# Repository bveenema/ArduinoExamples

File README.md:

# Mix Controller
A chrome extension user interface and embedded firmware for controlling mixing pumps.

#### Index
1. User Interface (Chrome Extension)
  * [Installation](#installation)
  * [Create Shortcuts](#create-shortcuts)
  * [How to Use](#how-to-use)
1. Firmware (Mixer Software)
  * [Driver Installation](#driver-installation)

## User Interface (Chrome Extension)
### Installation
To install the user interface:
1. Download the CRX file from the latest release
  - Go to [MixController/releases](https://github.com/bveenema/MixController/releases)
  - Click the **.crx** file in this *Assets* of the latest realese
  ![Img of where to download CRX file][JPG_downloadCRX]

2. Open the **Extensions** page in Chrome
![Type "chrome://extensions" in the address bar][JPG_GoToExtensions]

3. Install the App
  - Click and drag the CRX file into the *Extensions* window
  ![Install the App][JPG_installApp]

4. Accept the Permsions
  - Mix Controller requires access to your computers serial devices, click *Add App* to approve
  ![Img of Accept Permissions][JPG_acceptPermissions]

5. See [App Readme](https://github.com/bveenema/MixController/blob/master/Chrome%20Extension/README.md) for information on launching and using the app

### Create Shortcuts
To create Desktop/Start Menu/Taskbar shortcuts:
1. Click **Details** under Mix Controller, select **Create Shortcuts...** , select or deselect the shortcuts you want to create , click **Create**
![How to create shortcuts][JPG_CreateShortcuts]

## Firmware (Mixer Software)
### Driver Installation
In order to communicate with the Mixer Software, the drivers must be installed on first. Installing drivers is done by installing Particle CLI, a package of software that includes Particle drivers (which the Mixer Software runs on)

###### For Mac or Linux
---

Open Terminal, or preferred terminal program and paste this command to install the Particle CLI:

``` terminal
bash <( curl -sL https://particle.io/install-cli )
```

You may need to open a new terminal after the install completes to use the particle command.

If you get a message about installing dfu-util for your OS, make sure you have [homebrew](https://brew.sh/) installed and run the command above again.

###### For Windows
---
Download the [Windows CLI Installer](https://binaries.particle.io/cli/installer/windows/ParticleCLISetup.exe) and run it to install the Particle CLI, the device drivers and the dependencies that the CLI needs.

*Optional*: On the **Choose Components** screen, un-Select "CLI" and "OpenSSL (keys tools)" to install only the USB drivers.

[JPG_downloadZIP]: ReadmeAssets/DownloadZip.jpg "How to download ZIP"
[JPG_GoToExtensions]: ReadmeAssets/GoToExtensions.jpg "Or type \"chrome://extensions\" in the address bar"
[JPG_LoadUnpackedExtension]: ReadmeAssets/LoadUnpackedExtension.jpg "Check the box next to \"Developer Mode\" and then click \"Load unpacked extension\""
[JPG_MixControllerExtension]: ReadmeAssets/MixControllerExtension.jpg "Mix Controller Extension"
[JPG_CreateShortcuts]: ReadmeAssets/CreateShortcuts.jpg "How to create shortcuts"
[JPG_downloadCRX]: ReadmeAssets/downloadCRX.jpg "Where to download CRX"
[JPG_installApp]: ReadmeAssets/installApp.jpg "Click and drag to install"
[JPG_acceptPermissions]: ReadmeAssets/acceptPermission.jpg "Click Add App to accept serial permissions"

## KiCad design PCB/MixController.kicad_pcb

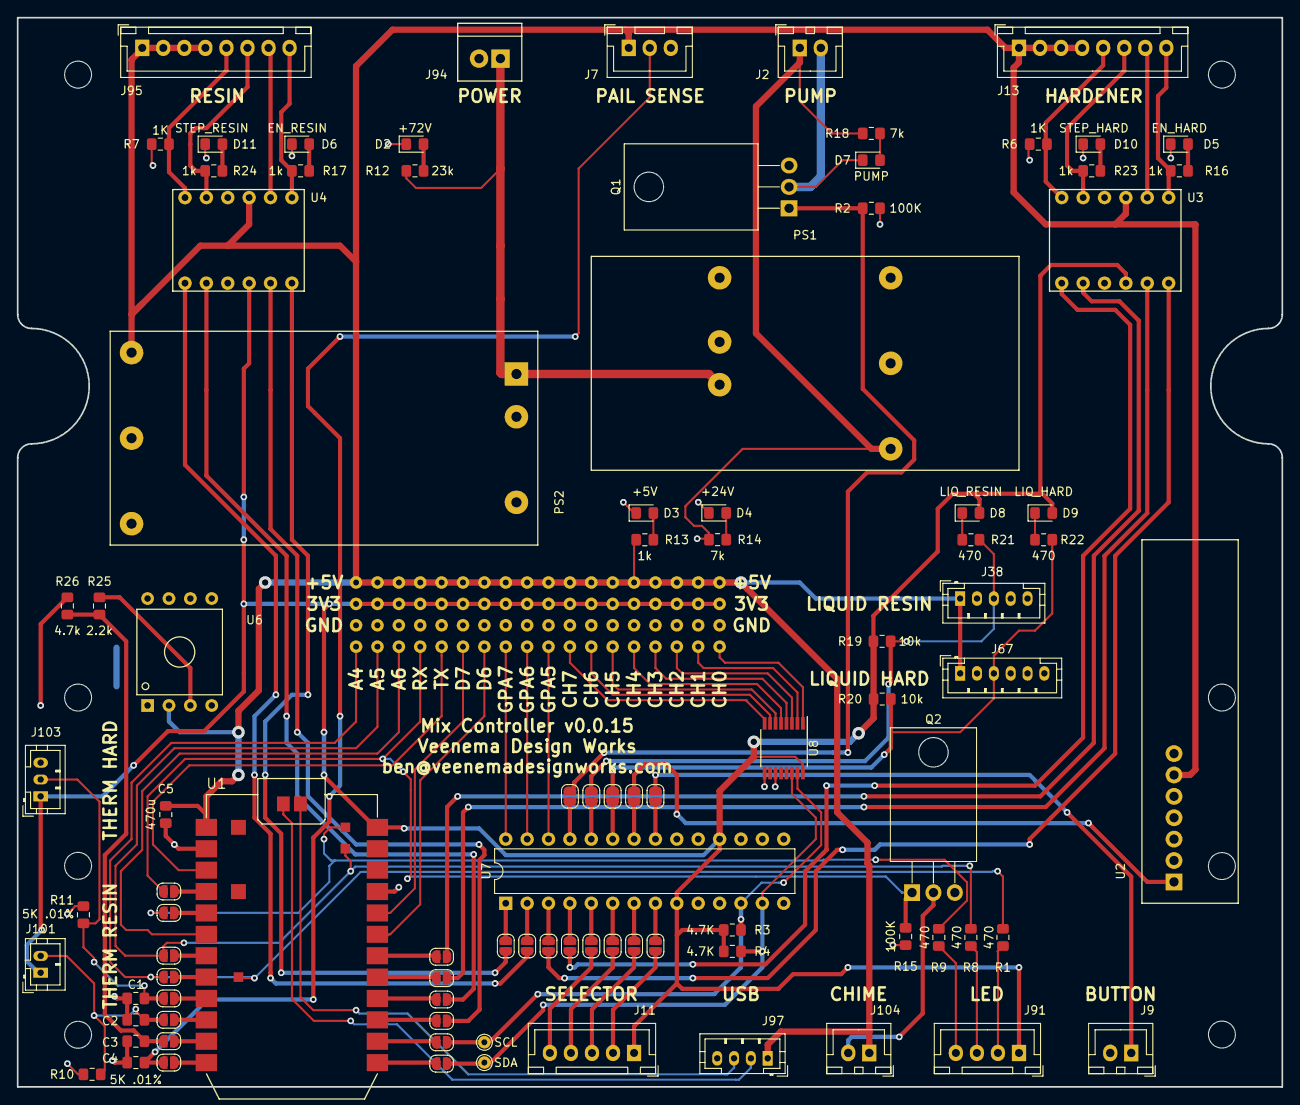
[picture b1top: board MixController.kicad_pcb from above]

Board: 2 copper layers, 150.2 x 127.0 mm, 166 parts (0 on the bottom side), 100 nets.

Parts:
C1, C2, C3, C4: 0.1u; C_0805_2012Metric_Pad1.15x1.40mm_HandSolder
C5: 470u; C_0805_2012Metric_Pad1.15x1.40mm_HandSolder
D2: +72V; LED_0805_2012Metric_Pad1.15x1.40mm_HandSolder
D3: +5V; LED_0805_2012Metric_Pad1.15x1.40mm_HandSolder
D4: +24V; LED_0805_2012Metric_Pad1.15x1.40mm_HandSolder
D5: EN_HARD; LED_0805_2012Metric_Pad1.15x1.40mm_HandSolder
D6: EN_RESIN; LED_0805_2012Metric_Pad1.15x1.40mm_HandSolder
D7: PUMP; LED_0805_2012Metric_Pad1.15x1.40mm_HandSolder
D8: LIQ_RESIN; LED_0805_2012Metric_Pad1.15x1.40mm_HandSolder
D9: LIQ_HARD; LED_0805_2012Metric_Pad1.15x1.40mm_HandSolder
D10: STEP_HARD; LED_0805_2012Metric_Pad1.15x1.40mm_HandSolder
D11: STEP_RESIN; LED_0805_2012Metric_Pad1.15x1.40mm_HandSolder
J2, J9, J104: B2B-XH-A(LF)(SN); JST_XH_B02B-XH-A_1x02_P2.50mm_Vertical
J7: B3B-XH-A(LF)(SN); JST_XH_B03B-XH-A_1x03_P2.50mm_Vertical
J11: B5B-XH-A(LF)(SN); JST_XH_B05B-XH-A_1x05_P2.50mm_Vertical
J13, J95: B8B-XH-A(LF)(SN); JST_XH_B08B-XH-A_1x08_P2.50mm_Vertical
J15, J16, J17, J18, J19, J20, J21, J22, J23, J24, J25, J26, J27, J28, J29, J30, J31, J32, J33, J34, J35, J36, J37, J39, J40, J41, J42, J43, J44, J45, J46, J47, J48, J49, J50, J51, J52, J53, J54, J56, J57, J58, J59, J60, J61, J62, J63, J64, J65, J66, J68, J69, J70, J72, J73, J74, J75, J76, J77, J78, J79, J80, J81, J82, J83, J84, J85, J86, J87, J88, J89, J90: ConnectorPoint_THT_D1.5mm_Drill-0.7mm
J38: B5B-PH-K-S(LF)(SN); JST_PH_B5B-PH-K_1x05_P2.00mm_Vertical
J67: B6B-PH-K-S(LF)(SN); JST_PH_B6B-PH-K_1x06_P2.00mm_Vertical
J91: B4B-XH-A(LF)(SN); JST_XH_B04B-XH-A_1x04_P2.50mm_Vertical
J94: 0705430001; Molex-705430001_02x2.54mm_Straight
J97: B4B-PH-K-S(LF)(SN); JST_PH_B4B-PH-K_1x04_P2.00mm_Vertical
J101: B2B-PH-K-S(LF)(SN); JST_PH_B2B-PH-K_1x02_P2.00mm_Vertical
J103: B3B-PH-K-S(LF)(SN); JST_PH_B3B-PH-K_1x03_P2.00mm_Vertical
JP1, JP2, JP3, JP4, JP5, JP6, JP7, JP8, JP9, JP10, JP11, JP12, JP13, JP14, JP15, JP16, JP17, JP18, JP19, JP20, JP21, JP22, JP23, JP24, JP25, JP26, JP27: SolderJumper-2_P1.3mm_Open_RoundedPad1.0x1.5mm
PS1: ERM01H110
PS2: RSDW20H-05; RSDW20_H
Q1, Q2: Q_NMOS_GDS; TO-220-3_Horizontal_TabDown
R1, R8, R9, R21, R22: 470; R_0805_2012Metric_Pad1.15x1.40mm_HandSolder
R2, R15: 100K; R_0805_2012Metric_Pad1.15x1.40mm_HandSolder
R3, R4: 4.7K; R_0805_2012Metric_Pad1.15x1.40mm_HandSolder
R6, R7: 1K; R_0805_2012Metric_Pad1.15x1.40mm_HandSolder
R10, R11: 5K .01%; R_0805_2012Metric_Pad1.15x1.40mm_HandSolder
R12: 23k; R_0805_2012Metric_Pad1.15x1.40mm_HandSolder
R13, R16, R17, R23, R24: 1k; R_0805_2012Metric_Pad1.15x1.40mm_HandSolder
R14, R18: 7k; R_0805_2012Metric_Pad1.15x1.40mm_HandSolder
R19, R20: 10k; R_0805_2012Metric_Pad1.15x1.40mm_HandSolder
R25: 2.2k; R_0805_2012Metric_Pad1.15x1.40mm_HandSolder
R26: 4.7k; R_0805_2012Metric_Pad1.15x1.40mm_HandSolder
TP1: SCL; TestPoint_THTPad_D1.5mm_Drill0.7mm
TP2: SDA; TestPoint_THTPad_D1.5mm_Drill0.7mm
U1: Photon; photon_smd
U2: Adafruit_1096; SimpleRF_Receiver
U3, U4: BOB-12009; BOB-12_W10.16mm
U6: HSCDANN005PGAA5; HoneyWell_DIP_AN
U7: MCP23017_SP; DIP-28_W7.62mm
U8: ADS7830; TSSOP-16_4.4x5mm_P0.65mm

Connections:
+3V3: D8.2, D9.2, J11.1, J20.1, J21.1, J22.1, J23.1, J24.1, J47.1, J48.1, J49.1, J50.1, J51.1, J52.1, J53.1, J54.1, J56.1, J57.1, J58.1, J87.1, J88.1, J91.1, J101.1, J103.1, R3.1, R4.1, R19.1, R20.1, U1.24, U3.4, U4.4, U7.9, U7.18, U8.16
+5V: C5.2, J7.1, J13.1, J13.2, J13.3, J13.4, J15.1, J16.1, J17.1, J18.1, J19.1, J30.1, J31.1, J32.1, J33.1, J34.1, J35.1, J36.1, J37.1, J38.1, J39.1, J40.1, J41.1, J67.1, J89.1, J90.1, J95.1, J95.2, J95.3, J95.4, J97.1, J104.1, PS2.3, R13.1, U1.1, U2.6, U3.9, U4.9, U6.2
+24V: J2.1, PS1.4, R14.2, R18.2
+72V: J94.1, PS1.1, PS2.1, R12.2
/CHIME: J43.1, JP26.1, Q2.1, R15.1
/HARDENER_ENABLE: JP8.1, U3.6
/HARDENER_HLFB: JP9.1, U3.1
/HARDENER_INPUT_DIR: JP19.2, U3.5
/HARDENER_INPUT_STEP: JP18.2, U3.2
/LIQUID_SNS_HARDENER: J67.3, JP16.1, R20.2, R22.1
/LIQUID_SNS_RESIN: J38.3, JP17.1, R19.2, R21.1
/PAIL_SNS: C4.2, J7.2, JP5.1
/PRESS_SNS: C3.2, JP4.1, R25.2, R26.1
/PUMP_EN: JP27.1, Q1.1, R2.1
/RESIN_ENABLE: JP6.1, U4.6
/RESIN_HLFB: JP7.1, U4.1
/RESIN_INPUT_DIR: JP21.2, U4.5
/RESIN_INPUT_STEP: JP20.2, U4.2
/ROTARY_1: J11.2, JP13.1
/ROTARY_2: J11.3, JP12.1
/ROTARY_3: J11.4, JP11.1
/ROTARY_4: J11.5, JP10.1
/SCL: JP22.2, R3.2, TP1.1, U7.12, U8.15
/SDA: JP23.2, R4.2, TP2.1, U7.13, U8.14
/STATUS_LED_B: JP1.1, R9.1, U1.29
/STATUS_LED_G: J45.1, JP2.1, R8.1, U1.28
/STATUS_LED_R: J46.1, JP3.1, R1.1, U1.27
/THERM_HARDENER: C1.2, J103.2, JP24.1, R11.1
/THERM_RESIN: C2.2, J101.2, JP25.1, R10.1
/USB(+): J97.2, U1.31
/USB(-): J97.3, U1.30
/USER_BUTTON: J9.1, JP14.1
/USER_REMOTE: JP15.1, U2.1
GND: C1.1, C2.1, C3.1, C4.1, C5.1, D2.1, D3.1, D4.1, D5.1, D6.1, D10.1, D11.1, J7.3, J9.2, J25.1, J26.1, J27.1, J28.1, J29.1, J38.2, J38.4, J59.1, J60.1, J61.1, J62.1, J63.1, J64.1, J65.1, J66.1, J67.2, J67.4, J68.1, J69.1, J70.1, J85.1, J86.1, J94.2, J97.4, PS1.2, PS1.6, PS2.2, PS2.5, Q1.3, Q2.3, R2.2, R6.1, R7.1, R10.2, R11.2, R15.2, R26.2, U1.2, U1.21, U2.7, U3.3, U3.10, U4.3, U4.10, U6.4, U7.10, U8.9, U8.11
unnamed: D2.2, R12.1
unnamed: D3.2, R13.2
unnamed: D4.2, R14.1
unnamed: D5.2, R16.2
unnamed: D6.2, R17.2
unnamed: D7.1, J2.2, Q1.2
unnamed: D7.2, R18.1
unnamed: D8.1, R21.2
unnamed: D9.1, R22.2
unnamed: D10.2, R23.2
unnamed: D11.2, R24.2
unnamed: J13.5, R6.2, U3.12
unnamed: J13.6, R23.1, U3.11
unnamed: J13.7, U3.8
unnamed: J13.8, R16.1, U3.7
unnamed: J42.1, U1.3
unnamed: J44.1, U1.6
unnamed: J72.1, U7.26
unnamed: J73.1, U7.27
unnamed: J74.1, U7.28
unnamed: J75.1, U8.1
unnamed: J76.1, U8.2
unnamed: J77.1, U8.3
unnamed: J78.1, U8.4
unnamed: J79.1, U8.5
unnamed: J80.1, U8.6
unnamed: J81.1, U8.7
unnamed: J82.1, U8.8
unnamed: J83.1, U1.20
unnamed: J84.1, U1.19
unnamed: J91.2, R1.2
unnamed: J91.3, R8.2
unnamed: J91.4, R9.2
unnamed: J95.5, R7.2, U4.12
unnamed: J95.6, R24.1, U4.11
unnamed: J95.7, U4.8
unnamed: J95.8, R17.1, U4.7
unnamed: J104.2, Q2.2
unnamed: JP1.2, U1.5
unnamed: JP2.2, U1.7
unnamed: JP3.2, U1.8
unnamed: JP4.2, U1.11
unnamed: JP5.2, U1.12
unnamed: JP6.2, U7.1
unnamed: JP7.2, U7.2
unnamed: JP8.2, U7.3
unnamed: JP9.2, U7.4
unnamed: JP10.2, U7.5
unnamed: JP11.2, U7.6
unnamed: JP12.2, U7.7
unnamed: JP13.2, U7.8
unnamed: JP14.2, U7.21
unnamed: JP15.2, U7.22
unnamed: JP16.2, U7.23
unnamed: JP17.2, U7.24
unnamed: JP18.1, U1.18
unnamed: JP19.1, U1.17
unnamed: JP20.1, U1.16
unnamed: JP21.1, U1.15
unnamed: JP22.1, U1.14
unnamed: JP23.1, U1.13
unnamed: JP24.2, U1.9
unnamed: JP25.2, U1.10
unnamed: JP26.2, U1.4
unnamed: JP27.2, U7.25
unnamed: R25.1, U6.3

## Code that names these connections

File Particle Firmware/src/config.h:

#ifndef CONFIG_H
#define CONFIG_H

#include <stdint.h>

#define THIS_PRODUCT_ID 7951
#define THIS_PRODUCT_VERSION 27

// Photon Pins
#define SDA_PIN D0
#define SCL_PIN D1
#define RESIN_INPUT_DIR_PIN D2
#define RESIN_INPUT_STEP_PIN D3
#define HARDENER_INPUT_DIR_PIN D4
#define HARDENER_INPUT_STEP_PIN D5

#define PAIL_SNS_PIN A0
#define PRESS_SNS_PIN A1
#define THERM_RESIN_PIN A2
#define THERM_HARDENER_PIN A3
#define STATUS_LED_R A4
#define STATUS_LED_G A5
#define STATUS_LED_B WKP
#define CHIME_PIN RX

// IOExp Pins
#define USER_BUTTON_IOEXP_PIN 0
#define USER_REMOTE_IOEXP_PIN 1
#define LIQUID_SNS_HARDENER_IOEXP_PIN 2
#define LIQUID_SNS_RESIN_IOEXP_PIN 3
#define PUMP_EN_IOEXP_PIN 4
#define LED_HARD_LIQ_IOEXP_PIN 5
#define LED_RESIN_LIQ_IOEXP_PIN 6

#define RESIN_ENABLE_IOEXP_PIN 8
#define RESIN_HLFB_IOEXP_PIN 9
#define HARDENER_ENABLE_IOEXP_PIN 10
#define HARDENER_HLFB_IOEXP_PIN 11
#define ROTARY_4_IOEXP_PIN 12
#define ROTARY_3_IOEXP_PIN 13
#define ROTARY_2_IOEXP_PIN 14
#define ROTARY_1_IOEXP_PIN 15

// Selector Switch Config
#define NUM_SELECTORS 5

// Status LED Settings
#define FAST_BLINK_RATE 150 // toggle every 250 ms
#define REGULAR_BLINK_RATE 750 // toggle every 750 ms

// Chime Settings
#define CHIME_FREQUENCY 3100 // 1100, 3100
#define CHIME_PULSE_TIME 250
#define CHIME_SLOW_RATE 3000
#define CHIME_MEDIUM_RATE 1500
#define CHIME_FAST_RATE 1000

// Temperature Monitor Settings
#define TEMPERATURE_CHECK_RATE 5000 // ms - temperature checking is slow, avoid calling frequently
#define TEMPERATURE_BETA_VALUE 3950
#define TEMPERATURE_FIXED_RESISTOR 4990 // ohms
#define TEMPERATURE_NOM_RESISTANCE 5000 // ohms
#define TEMPERATURE_NOM_CELCIUS 25.0 // degrees c
#define TEMPERATURE_NUM_SAMPLES 100 // number of adc samples in rolling average
#define TEMPERATURE_SAMPLE_RATE 10 // time between adc samples

// Pressure Charge Settings
// #define PRESSURE_ALWAYS_ON
#define PRESSURE_READ_RATE 10 // ms between reads of pressure sensor
#define MAX_CHARGE_PRESSURE 83000 // milli-inH20 ( 83000 = 3 PSI )
#define MAX_CHARGE_TIMEOUT 60000 // ms
#define PRESSURE_SENSOR_DELTA_P 138400 // Pmax-Pmin, 55.360 inH2O (2psi) 138.400 inH2O (5psi) 276.800 inH2O (10psi)
#define PRESSURE_SENSOR_PMIN 0 // Pmin 27.680 inH2O (1psi) 138.400 inH2O (5psi)
#define PRESSURE_SENSOR_VSUPPLY 3000 // 3.3 volts
#define DELAY_FOR_PUMP_TO_CHARGING_TRANSITION 500
#define DELAY_FOR_CHARGING_TO_PUMP_TRANSITION 500

// Pail Sensor Settings
#define DEFAULT_PAIL_DETECTION_THRESHOLD 600 // ADC Value (out of 4085)

// Mix Master Settings
#define TIME_BETWEEN_KEEP_OPEN_CYCLES 300000 // 5 minutes
#define FLUSH_FLOW_RATE 2000 // ml/min
#define FLUSH_MIN_TIME 30000 // ms
#define FLUSH_MAX_TIME 60000 // ms

// Pump Configuration
#define STEPS_PER_REV 200 

// Button and Remote Settings
// time must be held down to be a long press to initiate a "Flush" cycle
#define LONG_PRESS_TIME 3000

//  EEPROM Structure Definition
//    When changing the structure of EEPROM, increase THIS_EEPROM_VERSION, this
//    will cause EEPROM of previous versions to reset to default.
#define THIS_EEPROM_VERSION 25

struct prom_settings {
  uint32_t version;
  uint32_t stepsPerMlResin;
  uint32_t stepsPerMlHardener;
  uint32_t autoReverseSteps;
  uint32_t onPressure;
  uint32_t offPressure;
  uint32_t chargeTimeout;
  uint32_t chargeDelay;
  uint32_t keepOpenVolume;
  uint32_t pailThreshold;
  uint32_t maxPreMixChargingTime;
  uint32_t maxNoPressure;
  uint32_t primeVolume;
  uint32_t minPrimes;
  uint32_t minTemperature;
  uint32_t maxTemperature;
  uint32_t flushRPM;
  uint32_t washCycles;
  uint32_t flushCycles;
  uint32_t washCounts;
  uint32_t purgeCounts;
  uint32_t initialPurgeCounts;
  uint32_t chargeTime;
  uint32_t flushChargePressure;
  uint32_t flushChargeInterval;
  uint32_t flushPause;
  uint32_t flushFinishDelay;
  uint32_t zeroDripSteps;
  uint32_t zeroDripInterval;
  uint32_t maxTimeNoLiquid;
  // Selector Based Settings
  uint32_t flowRate[NUM_SELECTORS];
  uint32_t ratioResin[NUM_SELECTORS];
  uint32_t ratioHardener[NUM_SELECTORS];
  uint32_t volume[NUM_SELECTORS];
};

const uint32_t settingsAddr = 0;

const prom_settings defaultSettings = {
  THIS_EEPROM_VERSION,
  33, // stepsPerMlResin
  33, // stepsPerMlHardener
  175, // autoReverseSteps
  30448, // onPressure
  44288, // offPressure
  15000, // chargeTimeout
  1000, // chargeDelay
  150, // keepOpenVolume
  2000, // pailThreshold
  1000, // maxPreMixChargingTime
  1000, // maxNoPressure
  750, // primeVolume
  1, // minPrimes
  50, // minTemperature
  90, // maxTemperature
  200, // flushRPM
  50, // washCycles
  7, // flushCycles
  200, // washCounts
  1000, // purgeCounts
  3000, // initialPurgeCounts
  500, // chargeTime
  13840, // flushChargePressure (.5 PSI)
  2000, // flushChargeInterval
  0, // flushPause
  30000, // flushFinishDelay
  5, // zeroDripSteps
  1000, // zeroDripInterval
  3000, // maxTimeNoLiquid
  {3785,3785,3785,3785,3785}, // flowRate
  {0,200,100,231,204}, // ratioResin
  {0,100,400,100,100}, // ratioHardener
  {3785,3785,3785,3785,3785} // volume
};

#endif

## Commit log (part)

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2018-03-06 Restructure
2018-03-06 Update UI
2018-03-06 Add Download ZIP JPG
2018-03-06 Created Basic UI
2018-03-06 Added advanced section
2018-03-07 Split JS code and added Disabled Inputs on not Connected
2018-03-07 Updated Advanced Options
2018-03-08 Updated USB Serial Connection Protocol
2018-03-08 Updated Serial Protocol
2018-03-09 Updated Initial value retrieval and updateCurrentValue()
2018-03-09 Added memory for controller settings
2018-03-09 Updated serial interface
2018-03-10 Updated motion logic
2018-03-11 Added Error Handling
2018-03-12 Flipped STEP and DIR pins
2018-03-12 removed Internal pullup on button (using external 10k)
2018-03-20 Added button debounce and reversed dir pin
2018-04-02 Removed AutoReverse and Error Handling
2018-04-19 Added Schematic
2018-04-19 Create PDF of Schematic
2018-04-20 Removed extra Timer calls
2018-05-09 Re-enable StepsPerMlA/B
2018-05-14 Restructure Firmware Folder
2018-05-14 Create Packaged App
2018-05-14 Change to toggle button function
2018-05-14 Remove Bounce lib
2018-05-14 Add config.h
2018-05-15 Add Volume Control
2018-05-20 Updated Schematic
2018-05-23 Update default settings
2018-07-02 Update version number
2018-07-03 save all stashed
2018-07-03 Add Radio and Level Translator
2018-07-03 Add Level Translator
2018-07-03 Runs on startup. 1 min on, 30 sec off. Indefinetely
2018-07-18 Add Level Translators and box image
2018-07-18 Disable motors when not in use
2018-07-18 Change to version 0.0.3
2018-07-18 Cleanup packed Chrome Extensions
2018-08-09 Move pem file
2018-08-09 Add autoreverse, toggle pumps button and update to version 0.0.4
2018-08-09 Update CRX file
2018-08-23 Remove Switch and Relay, add Battery Connector
2018-08-28 Add Serial prints for button presses
2018-08-28 Update product id and version for chrome app
2018-08-28 Add "Message" to console logs for unknown variables
2018-08-29 Update FW to allow for multiple stored mixing configuration (untested)
2018-08-29 Fix selector updating
2018-08-29 Save place
2018-08-29 Fix selector variable name error
2018-08-29 Fix flag not clearing when no selector bug
2018-08-29 Enable multiple selectors with version 5+ FW
2018-08-29 Add Wifi toggling from app
2018-08-30 Fix selector switch detection
2018-08-30 Fix motorSettings not loading from EEPROM
2018-08-30 Add kicad backup file
2018-08-30 Add cable notes
2018-08-30 Add Rotary Selector
2018-08-30 Add version conditional showing of hidden elements
2018-08-30 Pack v0.0.5 extension
2018-08-30 No longer applicable
2018-08-30 Fix divide by 0 error when both motor ratios are 0 or flowRate is 0
2018-09-10 Move Serial Command interpreter to seperate file
2018-09-10 Separate global variables from ino
2018-09-10 Move serial reader to SerialSettings
2018-09-10 Remove SerialSetting variables from globals
2018-09-10 Fix disconnect from app bugs
2018-09-15 Update schematic with photo of selector
2018-09-15 Prep for v0.0.6
2018-09-16 Add WiFi.listening() protector to serial read
2018-09-16 Rename app and pdf to v0.0.6
2018-09-16 Create App ReadMe
2018-09-16 Update to new App installation procedure
2018-09-16 Fix link to App Readme
2018-09-16 Fix App Readme link
2018-09-21 Add checklist for v0.0.7
2018-09-22 Create Pneumatics Schematic
2018-09-22 Rename all "*A" to "*Resin" and "*B" to "*Hardener"
2018-09-22 Update Pins
2018-09-22 Rename "SerialSettings" to "AppInterface"
2018-09-23 Create MixMaster module. Remove Mixing function from main
2018-09-23 Add comments about using commandList
2018-09-23 Remove motor specific variables from globals
2018-09-23 Fix indentation
2018-09-23 Add "Cleaning" state
2018-09-23 Add long press to initiate cleaning cycle
2018-09-23 Rename all "motor" to "pump"
2018-09-23 Create idle, run and prepForMixing functions
2018-09-23 Cleaning runs at "correct" ratio
2018-09-23 Add flushing feature
2018-09-23 Fix naming error
2018-09-23 Complete keep open flush
2018-09-23 Create Pressure Manager
2018-09-23 Add Charging state to mixerState
2018-09-23 Add error checking for pumps
2018-09-23 Change "Motor Error" to "Pump Error"
2018-09-23 change mixMaster to MixMaster
2018-09-23 Add Status LED module
2018-09-23 Add 'chargePressure', 'flushVolume' and 'startCleaning' commands
2018-09-24 Save state - new hide/show element system
2018-09-24 Fix cleaning by default bug
2018-09-24 Fix bugs with MixMaster state
2018-09-24 Update getAllVariables() to ignore hidden
2018-09-24 Add chargPressure command
2018-09-24 Fix hide erorr when none
2018-09-24 Update Advanced options display
2018-09-24 Change the way action-buttons are handled
2018-09-25 Rename "Clean" to "Flush"
2018-09-25 Rename "Flush" to "Keep Open"
2018-09-25 Add Keep Open Volume
2018-09-27 Rename "Start Cleaning" to "Start Flush"
2018-09-27 Swap D6 and D7 pins
2018-09-27 Add current pressure output
2018-09-27 action-button disabling/enabling
2018-09-27 Add Dual State Button
2018-09-27 Fix Pressure Calculation
2018-09-27 Fix Long Press Remote on Startup (not in socket)
2018-09-27 All Caps all state names
2018-09-27 Typo fix
2018-09-27 Move Flow Rate and Volume to slider settings
2018-09-27 Create Pail Sensor
2018-09-27 Reduce max volume to 10,000ml (2.5 gallons)
2018-09-27 Update Flush Cycle to every minute and 1:1 ratio
2018-09-27 Handle fail to connect error
2018-09-28 Disable error checking on pumps
2018-09-28 Add fix list
2018-09-28 Create empty release directory
2018-09-29 Add 470 PD resistor to HV4 Inputs - Fix Pump Error
2018-09-29 Add Raw Pail Output
2018-09-29 Fix not updating detection threshold before restart
2018-09-29 Fix: Pail Sensor not stopping mixing/keep open
2018-09-29 Add: Kill cleaning if no pail
2018-09-29 Fix: Flushing was only working first cycle
2018-09-29 Update checklists
2018-09-29 Remove unneeded serial prints
2018-09-29 100 sample rolling average
2018-09-29 Remove voltage divider on pail sensor output
2018-09-30 Fix: Pump error detection
2018-09-30 Unneeded
2018-09-30 Cleanup
2018-10-01 Change blink configuration
2018-10-01 Add 10ms delay between pressure reads
2018-10-01 Add min charging time
2018-10-01 Make minChargingTime user settable
2018-10-01 settings.maxNoPressure user settable
2018-10-02 Add Priming
2018-10-02 Add primeing user interface
2018-10-02 Add pail sensor error checking
2018-10-02 Prevent charging error when flushing
2018-10-02 Update product verion to 8
2018-10-02 Pressure Pump Always On
2018-10-05 Add I/O and ADC Expanders
2018-10-07 Add footprints, Add connector between cable power and board
2018-10-08 Start Layout
2018-10-09 Continue Layout
2018-10-11 Add VDW-Kicad-Symbols
2018-10-11 Add knob note
2018-10-11 Update Libraries
2018-10-11 Remove backup
2018-10-12 Update Board Profile
2018-10-12 Update PCB Layout
2018-10-13 Switch to 200 steps/rev pump setting. Pump update called 10us interval
2018-10-13 Remove trial features, Wifi on triple long press and enable wifi after update
2018-10-13 Add incrementer for general debugging
2018-10-13 Disable incrementer for pump update
2018-10-13 Make PressureManager self declaring and including
2018-10-13 Move initial target pressure from constructor to init
2018-10-13 Enable charge pressure udpate via app
2018-10-13 Remove extra semi-colon
2018-10-15 Switch to 200 steps/rev motor setting. Pump stops while charging
2018-10-15 Remove out of date descriptor
2018-10-15 Add temporary voltage divider
2018-10-15 Change from target pressure to pressure window for charging
2018-10-15 Enable settings to have min and max version. Reuires min class first
2018-10-15 Update default values
2018-10-16 Add Spec hours
2018-10-16 Add app interface for Charging Timeout and Cool Down
2018-10-16 Add charging timeout and cooldown
2018-10-16 Fix typo {} was ()
2018-10-19 Create initial draft of ECM software spec
2018-10-22 Disabel PRESSURE_ALWAYS_ON
2018-10-22 Make chargeDelay user settable
2018-10-22 half update for Sperry changes
2018-10-23 Remove chargeCoolDown, replace with chargeOffTime
2018-10-23 Remove Charge Cool-Down Feature
2018-10-23 Remove minChargingTime, replace with maxPreMixChargingTime
2018-10-23 Regress to chargeTime and chargeOffTime functioning
2018-10-23 Clarify intention of setting
2018-10-23 rename app variables, increase max charge time to 60000
2018-10-23 disable, allowCharging while idle
2018-10-23 disable pump if charging not allowed
2018-10-23 Remove #ifndef flags
2018-10-24 Air pump off at beginning of wasCharging cycle
2018-10-24 complete list
2018-10-25 Change rolling average back to every 10ms for 1s
2018-10-25 Add delay after initial charge
2018-10-25 Fix mixing timer
2018-10-25 consolidate
2018-10-25 reduce accumulateError
2018-10-25 Change ON/OFF pressure to Low/High Pressure
2018-10-25 Update settings to match spec
2018-10-25 Add app settings to spec
2018-10-25 Add charging error time to spec
2018-10-25 Add unit for charging error time to spec
2018-10-29 Add indicator leds, chime speaker, update layout
2018-10-29 update todo
2018-10-30 Update Layout
2018-10-30 Update Footprint Library
2018-10-31 Update commit to track
2018-10-31 Add ignore files
2018-10-31 Finalize layout for v0.0.15
2018-10-31 add *.kicad_pcb-bak
2018-10-31 Change offboard component footprint from '~' to 'NoFootprint'
2018-10-31 Change out submodules to track master
2018-10-31 update footprints
2018-11-01 Add Knob component, change to LED Rocker Switch
2018-11-01 Update per ECN 10/31/18
2018-11-01 Add IOExp - MCP23017 object
2018-11-01 Capatalize "Remote" and "Button" objects
2018-11-01 Restructure setup
2018-11-01 Make StatusLED self instantiating
2018-11-02 Add FW pin numbers to MCP23017
2018-11-02 Switch to RGB LED
2018-11-02 Update comments
2018-11-02 Add 2 Red LEDs for Liquid Sensor status
2018-11-03 Add MCP address pin pull down resistors
2018-11-03 Create Liquid Sensor module
2018-11-03 Move selector switch to IOExp
2018-11-03 Typo correction
2018-11-03 Add reconfigure pins task
2018-11-04 Add Chime module
2018-11-04 Add TemperatureMonitor
2018-11-04 Remove pressure manager include
2018-11-04 Reduce IOExp calls
2018-11-04 Swap pin to IOExp
2018-11-04 Move Button and Remote to IOExp
2018-11-04 Fix RedLED off when no error
2018-11-04 Update ref to clickButton
2018-11-05 Fix maxTemperature setting
2018-11-05 Make SLOW chime for temperature range live
2018-11-05 Re-write Pressure Manager
2018-11-05 Re-write Mix Master
2018-11-05 Update FLUSH to rate of 2 liters for settable time 30-60 sec
2018-11-05 Add liquid sensor checking
2018-11-07 Update Submodule ref
2018-11-07 Fix Selector, update fixed resistor value
2018-11-07 add cabling notes
2018-11-09 Change chime freq to 3100
2018-11-09 Fix hasLiquid inverted
2018-11-09 Update cable lengths, add notes about solder bridge and radio replace
2018-11-14 Fix temperature range not set on startup
2018-11-14 Add maxTimeNoLiquid feature
2018-11-14 Update to v16
2018-12-05 Add VSCODE docs
2018-12-06 Implement new flush protocol
2018-12-06 Add Zero Drip
2018-12-06 Consolidate Enabling/Disabling of Pumps to prevent excessive IOExp calls
2018-12-09 Any button press in selector pos 0 initiates flush
2018-12-09 Change default flush reverse steps to 180
2018-12-09 Prevent ZeroDrip while in Flush selector position (0)
2018-12-09 Move ZeroDrip to new file. Change ZeroDrip only when no Pail
2018-12-09 Add DFU Mode button to App
2018-12-09 Update Kicad Symbols Ref
2018-12-15 Update Project
2018-12-15 Change to flush volume instead of time. Add Initial bolus for flush
2018-12-15 Add liquid checking for flush cycle
2018-12-15 Update default ZeroDrip Settings
2018-12-15 ZeroDrip runs regardless of bucket. Stops if KeepOpen stop due to bucket
2018-12-15 Fix Error with Advanced Settings
2018-12-16 Fix errors
2018-12-18 Add Camera Subsection
2018-12-24 Update Defaults
2018-12-24 Prevent KeepOpen and ZeroDrip while in flush selector position
2018-12-24 Update to version 20
2019-01-10 Update Submod
2019-01-16 Add Burp Time and Burp Pause
2019-01-16 Add forcePumpOn and forcePumpOff
2019-01-16 Add burp to wash cycle of flush
2019-01-17 Add Initial Purge Count feature
2019-01-29 Update Flush Cycle
2019-02-01 Flush stops on Liquid empty
2019-02-01 Add Interval Charging
2019-02-06 Add pump error detection and handling
2019-02-06 Temp add
